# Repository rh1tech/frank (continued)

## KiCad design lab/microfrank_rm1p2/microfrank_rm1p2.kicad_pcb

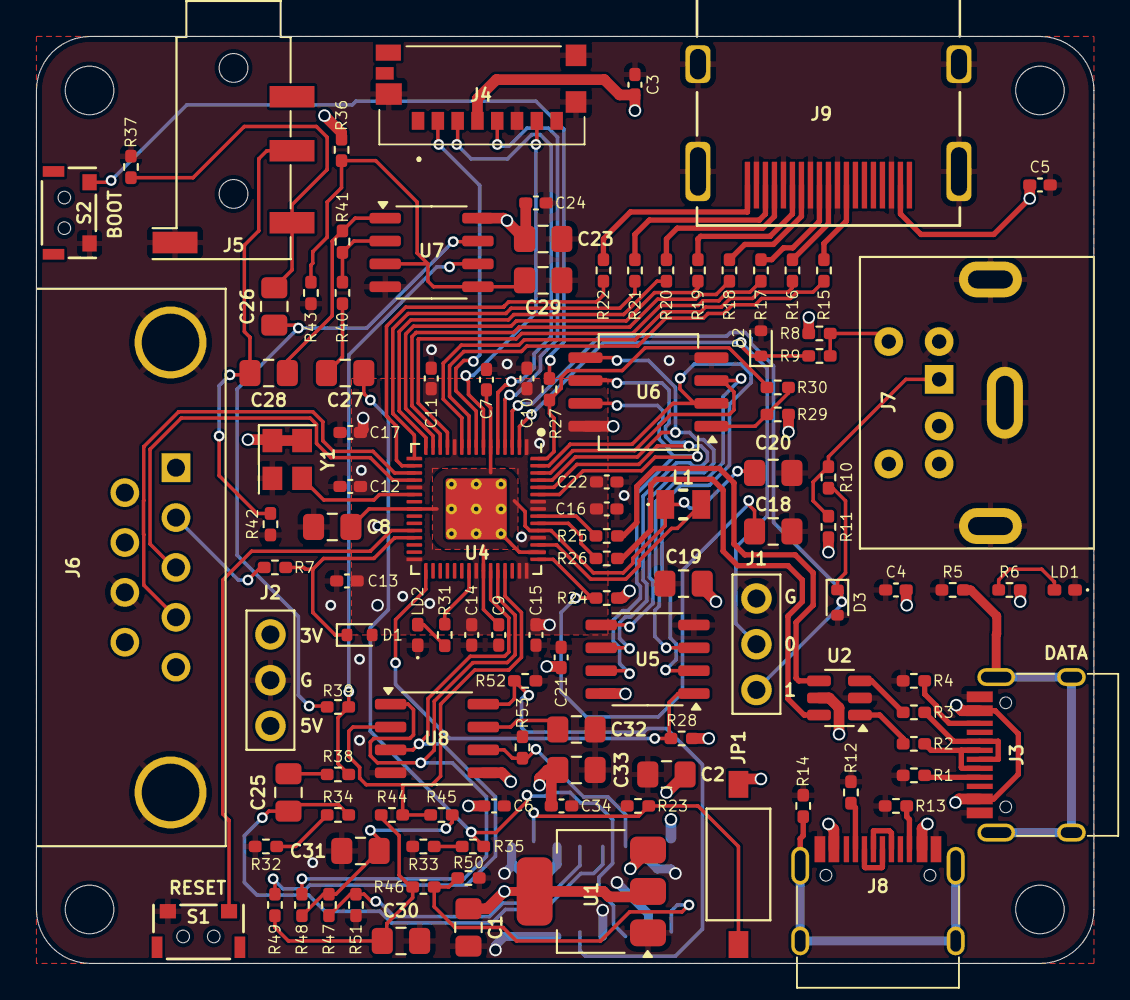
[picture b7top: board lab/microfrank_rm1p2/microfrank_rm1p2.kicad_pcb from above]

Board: 4 copper layers, 58.8 x 51.5 mm, 118 parts (1 on the bottom side), 88 nets.

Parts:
C1, C2, C23, C25, C26, C27, C28, C29, C32, C33: 10u; Capacitor (0805)
C3, C4, C5, C6, C7, C9, C10, C11, C12, C13, C14, C15, C16, C17, C21, C22, C24, C34: 100n; Capacitor (0402)
C8, C18, C19, C20: 4.7u; Capacitor (0805)
C30, C31: 47n; Capacitor (0805)
D1, D2, D3: 3V3; Diode (SOD-523)
H1, H2, H3, H4: MountingHole; Mounting Hole (2.7mm)
J1: UART; Pin Header (1x03)
J2: PWR; Pin Header (1x03)
J3, J8: USB4215-03-A; USB Type C
J4: 0475710001; MicroSD (SMD, short)
J5: PJ-320D; Jack (3.5mm, PJ-320D)
J6: D-SUB 9 Male; D-SUB (9 pin, male, top mount)
J7: MDC-036; MiniDIN (6 Pin, female)
J9: DC3RX19JA2; HDMI (female)
JP1: Main Jumpers; SW_DS04-254-2-01BK-SMT
L1: 3.3u; Inductor (0806)
LD1: Power; LED (0402)
LD2: Blue; LED (0402)
R1, R4, R12, R13: 5.1K; Resistor (0402)
R2, R3: 22R; Resistor (0402)
R5, R14: 1M; Resistor (0402)
R6, R7, R8, R11, R27, R31, R48, R49: 1K; Resistor (0402)
R9, R10: 100R; Resistor (0402)
R15, R16, R17, R18, R19, R20, R21, R22: 270R; Resistor (0402)
R23, R28, R29, R34, R35, R36, R38, R40, R43, R46, R47: 10K; Resistor (0402)
R24: 33R; Resistor (0402)
R25, R26: 27R; Resistor (0402)
R30: 0R; Resistor (0402)
R32, R33, R44, R45, R50, R51: 2K; Resistor (0402)
R37, R42: 20K; Resistor (0402)
R39, R41: 47K; Resistor (0402)
R52, R53: 470R; Resistor (0402)
S1: Reset; TACT-SIDE-4623
S2: TS-1233; TACT-SIDE-4623
U1: NCP1117 3.3; SOT-223
U2: USBLC6-2SC6; SOT-23-6
U3: 74HC4052D; SOP-16
U4: RP2350; QFN 60 (RP2350A)
U5: ESP-PSRAM32; SO-8
U6: W25Q128JVS; SOIC-8
U7: LM358; SO-8
U8: TDA1387T; SO-8
Y1: ASE-12MHz; Crystal (3225, active)

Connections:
+1V1: C7.1, C8.1, C9.1, C20.1, L1.1, U4.6 (DVDD), U4.23 (DVDD), U4.39 (DVDD), U4.50 (VREG_FB)
+3V3: C1.1, C3.2, C6.2, C10.1, C11.1, C12.1, C13.1, C14.1, C15.1, C16.1, C17.1, C19.1, C21.1, C22.1, J2.1, J4.P4 (VDD), JP1.2, R6.2, R24.1, R28.2, R29.1, U1.2 (VO), U3.16 (VCC), U4.1 (IOVDD), U4.11 (IOVDD), U4.20 (IOVDD), U4.30 (IOVDD), U4.38 (IOVDD), U4.44 (ADC_AVDD), U4.45 (IOVDD), U4.49 (VREG_VIN), U4.53 (USB_OTP_VDD), U4.54 (QSPI_IOVDD), U5.8 (VCC), U6.8 (VCC), Y1.1 (EN), Y1.4 (Vdd)
/AMP_IN_L: C25.1, R34.1, U3.13 (1Z)
/AMP_IN_R: C27.1, R35.1, U3.3 (2Z)
/AUDIOSW: JP1.1, R23.2, U3.10 (S0)
/Audio Out/AMP_OUTL: C26.2, J5.T, R37.2
/Audio Out/AMP_OUTR: C28.2, J5.R, R42.2
/GPIO0: D2.1 (K), J1.2, R9.2, U4.2 (GPIO0)
/GPIO1: D3.1 (K), J1.3, R10.2, U4.3 (GPIO1)
/GPIO2: J4.P5 (CLK), U4.4 (GPIO2)
/GPIO3: J4.P3 (CMD), U4.5 (GPIO3)
/GPIO4: J4.P7 (DAT0), U4.7 (GPIO4)
/GPIO5: J4.P2 (CD/DAT3), U4.8 (GPIO5)
/GPIO6: R15.2, U4.9 (GPIO6)
/GPIO7: R16.2, U4.10 (GPIO7)
/GPIO8: R17.2, U4.12 (GPIO8)
/GPIO9: R18.2, U4.13 (GPIO9)
/GPIO10: R19.2, U4.14 (GPIO10)
/GPIO11: R20.2, U4.15 (GPIO11)
/GPIO12: R21.2, U4.16 (GPIO12)
/GPIO13: R22.2, U4.17 (GPIO13)
/GPIO14: J6.4, U4.18 (GPIO14)
/GPIO15: J6.3, U4.19 (GPIO15)
/GPIO16: D1.1 (K), R7.1, U4.27 (GPIO16)
/GPIO19: R28.1, U4.31 (GPIO19), U5.1 (~CE)
/GPIO26: R49.2, U4.40 (GPIO26_ADC0), U8.3 (DATA)
/GPIO27: R48.2, U4.41 (GPIO27_ADC1), U8.1 (SCLK)
/GPIO28: R44.1, R45.1, U4.42 (GPIO28_ADC2), U8.2 (LRCK)
/KB_CLK: J7.5, R8.2, R9.1
/KB_DATA: J7.1, R10.1, R11.2
/PWM_OUT_L: R47.2, R51.1, U3.12 (1Y0)
/PWM_OUT_R: R46.2, R50.1, U3.1 (2Y0)
/PW_D+: R25.1, U2.4 (I/O2)
/PW_D-: R26.1, U2.6 (I/O1)
/RP2350A/FLASH_SS: R29.2, R30.2, U6.1 (~CS)
/RP2350A/QSPI_SCLK: U4.56 (QSPI_SCLK), U5.6 (SCLK), U6.6 (CLK)
/RP2350A/QSPI_SD0: U4.57 (QSPI_SD0), U5.5 (SI/SIO), U6.5 (DI(IO0))
/RP2350A/QSPI_SD1: U4.59 (QSPI_SD1), U5.2 (SO/SIO), U6.2 (DO(IO1))
/RP2350A/QSPI_SD2: U4.58 (QSPI_SD2), U5.3 (SIO2), U6.3 (IO2)
/RP2350A/QSPI_SD3: U4.55 (QSPI_SD3), U5.7 (SIO3), U6.7 (IO3)
/RP2350A/QSPI_SS: R27.1, R30.1, U4.60 (QSPI_SS)
/RP2350A/VREG_AVDD: C18.1, R24.2, U4.46 (VREG_AVDD)
/RP2350A/VREG_LX: L1.2, U4.48 (VREG_LX)
/RP2350A/XIN: U4.21 (XIN), Y1.3 (OUT)
/RP2350A/~USB_BOOT: R27.2, S2.2
/RUN: S1.1, U4.26 (RUN)
/TDA_L: R53.2, U3.14 (1Y1), U8.6 (A_LEFT)
/TDA_R: R52.1, U3.5 (2Y1), U8.8 (A_RIGHT)
GND: C1.2, C2.2, C3.1, C4.2, C5.2, C6.1, C7.2, C8.2, C9.2, C10.2, C11.2, C12.2, C13.2, C14.2, C15.2, C16.2, C17.2, C18.2, C19.2, C20.2, C21.2, C22.2, C23.1, C24.1, C29.1, C30.2, C31.2, C32.2, C33.2, C34.2, D1.2 (A), D2.2 (A), D3.2 (A), J1.1, J2.2, J3.1 (GND), J3.12 (GND), J4.G1 (GND_1), J4.G2 (GND_2), J4.G3 (GND_3), J4.P6 (VSS), J5.S, J6.8, J7.3, J8.1 (GND), J8.12 (GND), J9.2 (G_D2), J9.5 (G_D1), J9.8 (G_D0), J9.11 (G_CLK), J9.17 (G_DDC/CEC), J9.20 (SHIELD1), J9.21 (SHIELD2), J9.22 (SHIELD3), J9.23 (SHIELD4), LD1.1 (K), LD2.1 (K), R1.1, R4.1, R5.2, R12.1, R13.1, R14.2, R23.1, R32.2, R33.2, R37.1, R42.1, R43.1, R50.2, R51.2, R52.2, R53.1, S1.2, S2.1, U1.1 (GND), U2.2 (GND), U3.2 (2Y2), U3.4 (2Y3), U3.6 (~E), U3.7 (VEE), U3.8 (GND), U3.9 (S1), U3.11 (1Y3), U3.15 (1Y2), U4.47 (VREG_PGND), U4.61 (GND), U5.4 (VSS), U6.4 (GND), U7.4 (V-), U8.4 (AGND), Y1.2 (GND)
GPIO25: R31.2, U4.37 (GPIO25)
unnamed: C25.2, R38.2
unnamed: C26.1, R39.1, U7.7
unnamed: C27.2, R40.2
unnamed: C28.1, R41.1, U7.1
unnamed: C30.1, R44.2, R46.1, R49.1
unnamed: C31.1, R45.2, R47.1, R48.1
unnamed: J3.4 (CC1), R1.2
unnamed: J3.10 (CC2), R4.2
unnamed: J3.5 (DN2), J3.7 (DN1), R2.2
unnamed: J3.6 (DP1), J3.8 (DP2), R3.2
unnamed: J3.13 (SHIELD), R5.1
unnamed: J6.2, R7.2
unnamed: J8.4 (CC1), R12.2
unnamed: J8.10 (CC2), R13.2
unnamed: J8.5 (DN2), J8.7 (DN1)
unnamed: J8.6 (DP1), J8.8 (DP2)
unnamed: J8.13 (SHIELD), R14.1
unnamed: J9.12 (CLKN), R15.1
unnamed: J9.10 (CLKP), R16.1
unnamed: J9.9 (D0N), R17.1
unnamed: J9.7 (D0P), R18.1
unnamed: J9.6 (D1N), R19.1
unnamed: J9.4 (D1P), R20.1
unnamed: J9.3 (D2N), R21.1
unnamed: J9.1 (D2P), R22.1
unnamed: LD1.2 (A), R6.1
unnamed: LD2.2 (A), R31.1
unnamed: R2.1, U2.1 (I/O1)
unnamed: R3.1, U2.3 (I/O2)
unnamed: R32.1, R34.2
unnamed: R33.1, R35.2
unnamed: R26.2, U4.51 (USB_DM)
unnamed: R25.2, U4.52 (USB_DP)
unnamed: C29.2, R36.1, R43.2, U7.3 (+), U7.5 (+)
unnamed: R40.1, R41.2, U7.2 (-)
unnamed: R38.1, R39.2, U7.6 (-)
unnamed: C32.1, U8.7 (FLT)
VBUS: C2.1, C4.1, C5.1, C23.2, C24.2, C33.1, C34.1, J2.3, J3.2 (VBUS), J3.11 (VBUS), J6.6, J7.4, J8.2 (VBUS), J8.11 (VBUS), J9.18 (+5V), R8.1, R11.1, R36.2, U1.3 (VI), U2.5 (VBUS), U7.8 (V+), U8.5 (VA)

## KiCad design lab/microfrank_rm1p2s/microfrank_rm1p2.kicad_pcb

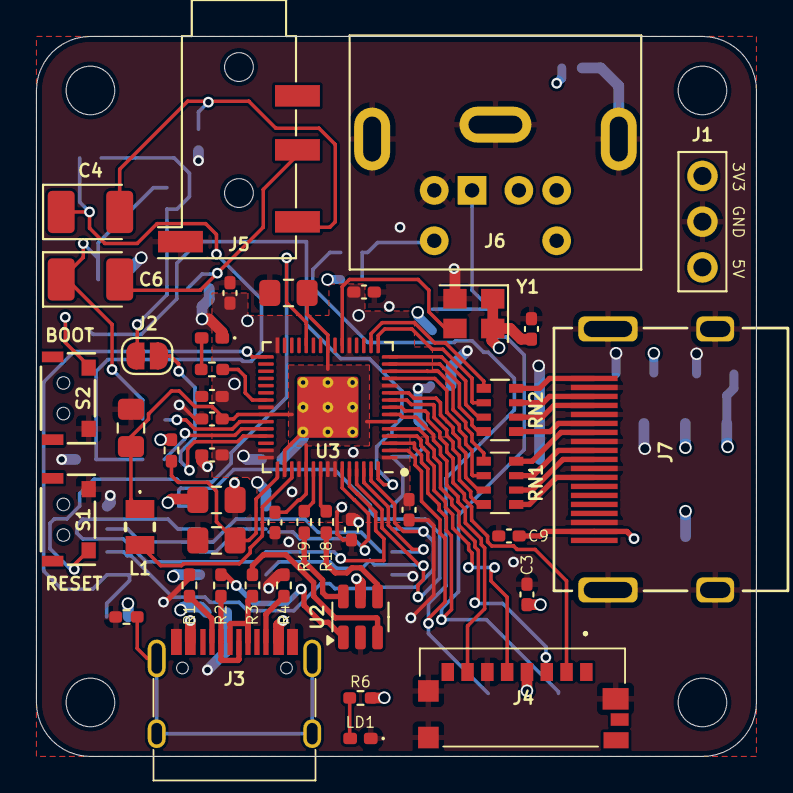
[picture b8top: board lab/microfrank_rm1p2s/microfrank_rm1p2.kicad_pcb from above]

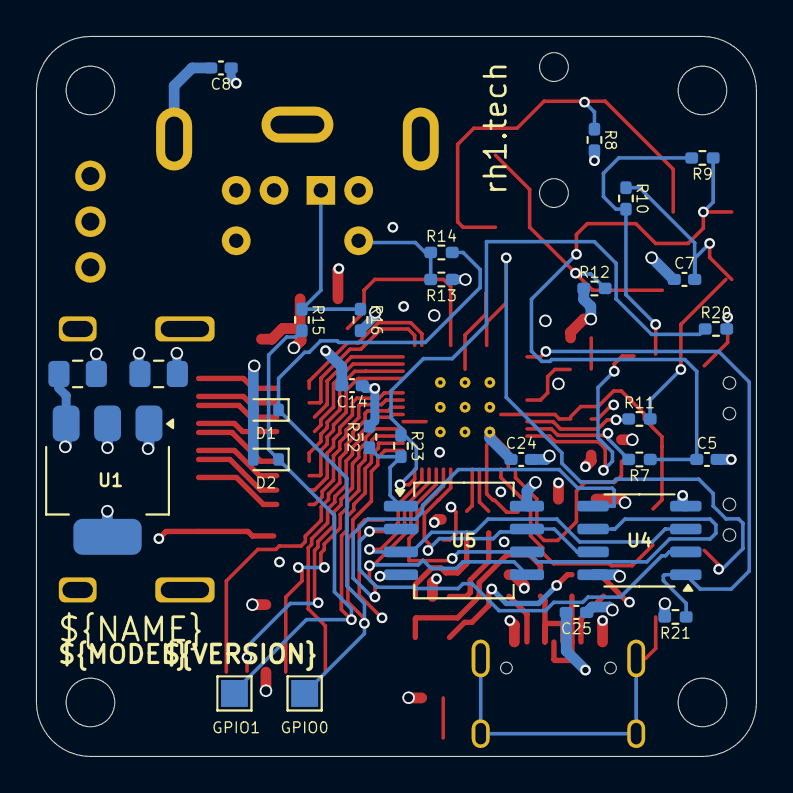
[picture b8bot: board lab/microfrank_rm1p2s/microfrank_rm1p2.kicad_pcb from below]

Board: 4 copper layers, 40.0 x 40.0 mm, 77 parts (29 on the bottom side), 63 nets.

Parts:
C1, C2: 10u; Capacitor (0805)
C3, C8, C9, C10, C12, C13, C14, C15, C16, C17, C18, C19, C20, C24, C25: 100n; Capacitor (0402)
C4, C6: 10u; Capacitor (3528, tantalum, polar)
C5, C7: 10n; Capacitor (0402)
C11, C21, C22, C23: 4.7u; Capacitor (0805)
D1, D2: 3V3; Diode (SOD-523)
H1, H2, H3, H4: MountingHole; Mounting Hole (2.7mm)
J1: PWR; Pin Header (1x03)
J2: BEEP; Jumper (solder)
J3: USB4215-03-A; USB Type C
J4: 0475710001; MicroSD (SMD, short)
J5: PJ-320D; Jack (3.5mm, PJ-320D)
J6: MDC-036; MiniDIN (6 Pin, female)
J7: DC3RX19JA2; HDMI (female)
L1: 3.3u; Inductor (0806)
LD1: Power; LED (0402)
LD2: Blue; LED (0402)
R1, R4: 5.1K; Resistor (0402)
R2, R3: 22R; Resistor (0402)
R5: 1M; Resistor (0402)
R6, R13, R16, R20, R24: 1K; Resistor (0402)
R7, R11: 1k; Resistor (0402)
R8, R12: 330R; Resistor (0402)
R9, R10: 2k; Resistor (0402)
R14, R15: 100R; Resistor (0402)
R17: 33R; Resistor (0402)
R18, R19: 27R; Resistor (0402)
R21, R22: 10K; Resistor (0402)
R23: 0R; Resistor (0402)
RN1, RN2: 270R; Resistor Array (4x0603)
S1: Reset; TACT-SIDE-4623
S2: TS-1233; TACT-SIDE-4623
TP1, TP2: GPIO0; Test Point (Pad, 1.5x1.5mm)
U1: NCP1117 3.3; SOT-223
U2: USBLC6-2SC6; SOT-23-6
U3: RP2350; QFN 60 (RP2350A)
U4: ESP-PSRAM32; SO-8
U5: W25Q128JVS; SOIC-8
Y1: ASE-12MHz; Crystal (3225, active)

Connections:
+1V1: C10.1, C11.1, C12.1, C23.1, L1.1, U3.6 (DVDD), U3.23 (DVDD), U3.39 (DVDD), U3.50 (VREG_FB)
+3V3: C1.1, C3.2, C13.1, C14.1, C15.1, C16.1, C17.1, C18.1, C19.1, C20.1, C22.1, C24.1, C25.1, J1.1, J4.P4 (VDD), R6.2, R17.1, R21.2, R22.1, U1.2 (VO), U3.1 (IOVDD), U3.11 (IOVDD), U3.20 (IOVDD), U3.30 (IOVDD), U3.38 (IOVDD), U3.44 (ADC_AVDD), U3.45 (IOVDD), U3.49 (VREG_VIN), U3.53 (USB_OTP_VDD), U3.54 (QSPI_IOVDD), U4.8 (VCC), U5.8 (VCC), Y1.1 (EN), Y1.4 (Vdd)
/Audio Out/AMP_OUTL: C4.2, J5.T, R8.1
/Audio Out/AMP_OUTR: C6.2, J5.R, R12.1
/BEEP_OUT: J2.1, R9.2, R10.2
/GPIO0: D1.1 (K), R14.2, TP1.1, U3.2 (GPIO0)
/GPIO1: D2.1 (K), R15.2, TP2.1, U3.3 (GPIO1)
/GPIO2: J4.P5 (CLK), U3.4 (GPIO2)
/GPIO3: J4.P3 (CMD), U3.5 (GPIO3)
/GPIO4: J4.P7 (DAT0), U3.7 (GPIO4)
/GPIO5: J4.P2 (CD/DAT3), U3.8 (GPIO5)
/GPIO6: RN1.4 (R4.1), U3.9 (GPIO6)
/GPIO7: RN1.3 (R3.1), U3.10 (GPIO7)
/GPIO8: RN1.2 (R2.1), U3.12 (GPIO8)
/GPIO9: RN1.1 (R1.1), U3.13 (GPIO9)
/GPIO10: RN2.4 (R4.1), U3.14 (GPIO10)
/GPIO11: RN2.3 (R3.1), U3.15 (GPIO11)
/GPIO12: RN2.2 (R2.1), U3.16 (GPIO12)
/GPIO13: RN2.1 (R1.1), U3.17 (GPIO13)
/GPIO19: R21.1, U3.31 (GPIO19), U4.1 (~CE)
/GPIO26: R11.2, U3.40 (GPIO26_ADC0)
/GPIO27: R7.2, U3.41 (GPIO27_ADC1)
/GPIO28: J2.2, U3.42 (GPIO28_ADC2)
/KB_CLK: J6.5, R13.2, R14.1
/KB_DATA: J6.1, R15.1, R16.2
/PW_D+: R18.1, U2.4 (I/O2)
/PW_D-: R19.1, U2.6 (I/O1)
/RP2350A/FLASH_SS: R22.2, R23.2, U5.1 (~CS)
/RP2350A/QSPI_SCLK: U3.56 (QSPI_SCLK), U4.6 (SCLK), U5.6 (CLK)
/RP2350A/QSPI_SD0: U3.57 (QSPI_SD0), U4.5 (SI/SIO), U5.5 (DI(IO0))
/RP2350A/QSPI_SD1: U3.59 (QSPI_SD1), U4.2 (SO/SIO), U5.2 (DO(IO1))
/RP2350A/QSPI_SD2: U3.58 (QSPI_SD2), U4.3 (SIO2), U5.3 (IO2)
/RP2350A/QSPI_SD3: U3.55 (QSPI_SD3), U4.7 (SIO3), U5.7 (IO3)
/RP2350A/QSPI_SS: R20.1, R23.1, U3.60 (QSPI_SS)
/RP2350A/VREG_AVDD: C21.1, R17.2, U3.46 (VREG_AVDD)
/RP2350A/VREG_LX: L1.2, U3.48 (VREG_LX)
/RP2350A/XIN: U3.21 (XIN), Y1.3 (OUT)
/RP2350A/~USB_BOOT: R20.2, S2.2
/RUN: S1.1, U3.26 (RUN)
GND: C1.2, C2.2, C3.1, C5.2, C7.2, C8.2, C9.2, C10.2, C11.2, C12.2, C13.2, C14.2, C15.2, C16.2, C17.2, C18.2, C19.2, C20.2, C21.2, C22.2, C23.2, C24.2, C25.2, D1.2 (A), D2.2 (A), J1.2, J3.1 (GND), J3.12 (GND), J4.G1 (GND_1), J4.G2 (GND_2), J4.G3 (GND_3), J4.P6 (VSS), J5.S, J6.3, J7.2 (G_D2), J7.5 (G_D1), J7.8 (G_D0), J7.11 (G_CLK), J7.17 (G_DDC/CEC), J7.20 (SHIELD1), J7.21 (SHIELD2), J7.22 (SHIELD3), J7.23 (SHIELD4), LD1.1 (K), LD2.1 (K), R1.1, R4.1, R5.2, R8.2, R12.2, S1.2, S2.1, U1.1 (GND), U2.2 (GND), U3.47 (VREG_PGND), U3.61 (GND), U4.4 (VSS), U5.4 (GND), Y1.2 (GND)
GPIO25: R24.2, U3.37 (GPIO25)
unnamed: C4.1, C5.1, R7.1, R9.1
unnamed: C6.1, C7.1, R10.1, R11.1
unnamed: J3.4 (CC1), R1.2
unnamed: J3.10 (CC2), R4.2
unnamed: J3.5 (DN2), J3.7 (DN1), R2.2
unnamed: J3.6 (DP1), J3.8 (DP2), R3.2
unnamed: J3.13 (SHIELD), R5.1
unnamed: J7.12 (CLKN), RN1.5 (R4.2)
unnamed: J7.10 (CLKP), RN1.6 (R3.2)
unnamed: J7.9 (D0N), RN1.7 (R2.2)
unnamed: J7.7 (D0P), RN1.8 (R1.2)
unnamed: J7.6 (D1N), RN2.5 (R4.2)
unnamed: J7.4 (D1P), RN2.6 (R3.2)
unnamed: J7.3 (D2N), RN2.7 (R2.2)
unnamed: J7.1 (D2P), RN2.8 (R1.2)
unnamed: LD1.2 (A), R6.1
unnamed: LD2.2 (A), R24.1
unnamed: R2.1, U2.1 (I/O1)
unnamed: R3.1, U2.3 (I/O2)
unnamed: R19.2, U3.51 (USB_DM)
unnamed: R18.2, U3.52 (USB_DP)
VBUS: C2.1, C8.1, C9.1, J1.3, J3.2 (VBUS), J3.11 (VBUS), J6.4, J7.18 (+5V), R13.1, R16.1, U1.3 (VI), U2.5 (VBUS)
